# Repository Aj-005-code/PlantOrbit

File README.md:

# PlantOrbit-Sim — simulation of a self-calibrating orbital plant-imaging robot

**Everything in this project is SIMULATED.** No number here was measured on hardware. Never describe
these results as experimental or measured results in a patent specification, pitch or paper.

## 1. What the simulation is meant to support

The narrowed invention (see the earlier discussion) has three linked parts:

1. **Self-calibration** — a wheeled robot measures the pot (ranging-sensor scan + robust circle fit) and
   computes its own orbit radius and station list. No hardcoded pot size.
2. **Repeatable station poses** — the robot returns to the same angular stations every session. Dead
   reckoning drifts, so a fiducial (printed-marker) pose fix on the mat bounds the error.
3. **Multi-view change detection** — images taken at the *same* stations on different days are compared;
   an alert needs agreement from at least *k* of the 12 stations.

The three experiments test one question each:

| Exp | Question | Script |
|---|---|---|
| 1 | Does the scan + fit recover the pot radius for different pot sizes, with noise and leaf outliers? | `experiments/exp1_calibration.py` |
| 2 | Does the fiducial correction keep station poses repeatable where dead reckoning drifts? | `experiments/exp2_repeatability.py` |
| 3 | Does that repeatability reduce false alarms in image-based change detection while keeping detection power? | `experiments/exp3_change_detection.py` |

## 2. Environment setup (step by step)

Requirements: Python 3.10 or newer (built and tested on 3.12), about 500 MB disk, any OS, no GPU.

```bash
# 1. unzip the project and enter it
cd plantorbit-sim

# 2. create an isolated environment
python -m venv .venv
#   Windows PowerShell:  .venv\Scripts\Activate.ps1
#   Windows cmd:         .venv\Scripts\activate.bat
#   macOS / Linux:       source .venv/bin/activate

# 3. install pinned-minimum dependencies
pip install -r requirements.txt

# 4. run the tests (should print: 6 passed)
python -m pytest -q tests

# 5. run everything (about 4 minutes on a laptop CPU)
python run_all.py
```

Outputs appear in `results/`:

- `SUMMARY.md` — readable tables; `summary.json` — all numbers
- `exp*.csv` — raw and aggregated data (every table in your documents should trace to one of these)
- `figures/fig0..fig4*.png` — layout, calibration, repeatability, alert rates, station montage
- `environment.json` — library versions, full config, timestamp, SHA-256 hash of every result file

## 3. Code map

| File | Role |
|---|---|
| `orbitsim/config.py` | **Every assumption in one place** (sensor noise, slip, gyro drift, marker noise, thresholds) |
| `orbitsim/calibration.py` | Simulated ToF scan, least-squares and RANSAC circle fit, imaging radius, station generation |
| `orbitsim/robot.py` | Differential-drive model with separate TRUE and ESTIMATED pose; fiducial correction; session runner |
| `orbitsim/plant.py` | Procedural 3-D plant, five change scenarios, pinhole camera renderer, camera framing |
| `orbitsim/detect.py` | Pot-rim alignment, plant segmentation, per-station metrics, alert rules |
| `orbitsim/stats.py` | Wilson confidence interval, summary statistics |
| `experiments/` | The three experiments plus the layout figure |
| `tests/test_core.py` | Sanity tests (exact circle fit, zero-noise robot hits every station, markers help, determinism) |
| `run_all.py` | Runs everything and records a reproducibility manifest |

To change an assumption, edit `config.py` (for example `gyro_bias_sigma_dps`) and re-run. Every random
draw is seeded from `Config.seed`, so identical code and config give identical results.

## 4. Results from the final run (seed 20261011)

### Experiment 1 — calibration (500 random pots, radius 30–120 mm, offset up to 15 mm; 3 mm noise, 5 % dropout, 8 % leaf outliers)

- Robust (RANSAC) fit: radius error median 0.27 mm, 95th percentile 0.82 mm, max 1.27 mm; 100 % within 3 mm.
- Plain least squares on the same scans: only 69 % within 3 mm, because leaf outliers bias it.
- **Honest finding:** with *no* outliers and high sensor noise (6–10 mm), plain least squares is slightly
  *better* than RANSAC (for example 10 mm noise, no outliers: median 1.0 mm vs 1.95 mm), because the 6 mm
  inlier tolerance throws away good points. The robust fit pays off only when outliers exist. Tune
  `ransac_tol_mm` to your real sensor once measured.

### Experiment 2 — repeatability (200 sessions per mode, 12 stations, assumed hobby-grade robot)

| Mode | Mean position error | 95th pct | Same-station offset between two sessions, 95th pct |
|---|---|---|---|
| Dead reckoning (gyro + encoders, dock-homed) | 7.6 mm | 17.5 mm | 26.4 mm |
| Fiducial-corrected | 1.7 mm | 3.3 mm | 4.7 mm |

- Dead-reckoning error grows along the orbit (Fig. 2); the fiducial-corrected error stays flat.
- Sensitivity: with a 10× worse gyro bias (0.1 °/s), dead-reckoning mean error rises to 15.5 mm (95th pct 46 mm)
  while the corrected mode is unchanged (1.6 mm). The corrected mode scales with marker measurement noise
  instead (1 mm noise → 1.1 mm error; 5 mm → 5.5 mm).
- **Assumption warning:** these numbers depend entirely on the noise model in `config.py`. A better gyro,
  a stepper-based drive or a mechanical guide ring would shrink the dead-reckoning baseline. The
  comparison is "naive dead reckoning vs fiducial correction", not "every possible alternative".

### Experiment 3 — change detection (40 random plants, 5 scenarios, 12 stations, alert needs ≥ 3 stations)

| Scenario | Ideal poses | Dead reckoning | Fiducial-corrected |
|---|---|---|---|
| none (must NOT alert) | 0 % | **45 %** | 0 % |
| growth (must NOT alert) | 0 % | 5 % | 0 % |
| leaf drop (should alert) | 85 % | 90 % | 93 % |
| yellowing (should alert) | 100 % | 100 % | 100 % |
| wilting (should alert) | 100 % | 100 % | 100 % |

- The key result is the **false-alarm rate on an unchanged plant**: 45 % with dead reckoning versus 0/40
  (95 % interval 0–9 %) with fiducial correction.
- Read the dead-reckoning detection rates with care: they are inflated, because that mode raises alerts
  even when nothing changed. Detection power only means something together with the false-alarm rate.
- Threshold sweep (`exp3_threshold_sweep.csv`, area threshold 0.06): requiring more stations to agree cuts
  dead-reckoning false alarms (44 % at k=1, 25 % at k=3, 9 % at k=5) but never reaches the corrected mode's 0 %.
  Corrected-mode detection stays at 92–98 % across k=1–5.
- Leaf-drop detection (about 93 %) is the weakest case, since removing 3 of 22 leaves changes few pixels
  from some angles. Treat 40 trials as a small sample; the intervals in `exp3_alert_rates.csv` are wide.

## 5. Development log (keep this kind of record — it is good practice and honest)

1. **First full run:** the corrected mode and even the *ideal* mode showed 12–17 % false alarms on
   unchanged plants.
2. **Diagnosis** (inspecting `exp3_raw_metrics.csv` and a rendered frame): the camera framing left only a
   thin sliver of the pot in view, so the pot-rim alignment anchor was unstable and sometimes misaligned
   the image pair. This was a flaw in my set-up, not in the idea.
3. **Fixes:** (a) camera height and tilt are now chosen once per plant so canopy and pot rim both fit
   (`plant.framing`); (b) alignment is skipped when fewer than 300 pot pixels are visible or the proposed
   shift exceeds 25 px; (c) focal length changed 250 → 220 px for a wider field of view.
4. **Re-validation:** the fix was checked on a separate development seed (`seed+33`), then the final
   experiment was run on a **fresh test seed (`seed+4`)** so results were not tuned on the data reported.
5. Thresholds (6 % area, 8 % yellow, 8 % canopy-top, k=3) were set a priori, not fitted to results; the
   sweep CSV shows sensitivity to them.

## 6. What this simulation does and does NOT show

**It supports:** the algorithms are logically consistent and workable; fiducial correction should bound
pose error under the assumed noise; bounded pose error should reduce false alarms in multi-view
comparison; calibration adapts to pot size without manual coordinates.

**It does not show:** real sensor behaviour (ToF returns off glossy pots, fiducial detection under glare,
shadows, wind or watering changes); real plant appearance (the plant is a simple procedural model, not a
photograph of a living plant); non-circular pots (square or tapered pots break the circle assumption);
marker visibility from all 12 stations (assumed: at least two fiducials are always visible to a pose
camera, which is a hardware design detail to settle); real drift (measure your own robot).

## 7. Patent-readiness checklist

Not legal advice — confirm every step with a registered patent agent.

1. **Do not disclose before filing.** No GitHub push, video, post or paper until the provisional is filed.
2. **Version control privately:** `git init`, commit this project, `git tag sim-v1-final-run`. Commit
   timestamps give a dated record of what you had and when. Keep the repo private.
3. **Inventor's notebook:** one dated entry per work session (what you tried, what failed, what changed).
   Section 5 above is the model. Record who contributed which idea — inventorship matters.
4. **Check your institution's IP policy** (VIT) before using lab space, funds or staff time.
5. **Archive the run:** keep `results/environment.json` (library versions, config, file hashes) and the
   exact zip you worked from.
6. **Map results to the provisional specification:**

| Specification section | Source in this project |
|---|---|
| Background / problem | Fixed-coordinate systems fail across pot sizes; dead reckoning drifts; single-image checks miss trends |
| Summary of the invention | Sections 1 and 3 of this README |
| Brief description of drawings | `fig0_layout`, flowcharts you draw from `calibration.py` and `robot.py`, block diagram, pin diagram |
| Detailed description / enablement | The algorithms, parameters and assumptions in `config.py`, written out in words and pseudocode |
| Examples | Experiments 1–3, **explicitly labelled as simulation**, with the noise model stated |
| Claims | Method claims: scan → fit → derive orbit; fiducial-corrected station revisit; same-station multi-view comparison with k-of-n agreement. Draft with your agent. |

7. **Plot figures properly:** the PNGs here are evidence figures, not formal patent drawings. Formal drawings
   are black-and-white line drawings; your agent will advise.
8. **Prior art:** the earlier search was informal. A professional IPC-coded search is still needed before
   finalising claims, and linear-rail repeatable-pose systems (found earlier) are the closest art to
   distinguish against.
9. **File order:** DPIIT startup registration → provisional application at ipindiaonline.gov.in →
   12 months to replace simulated evidence with measured data and file the complete specification.

## 8. Replacing each assumption with a measurement (the next 12 months)

| Simulated assumption (`config.py`) | How to measure it on hardware |
|---|---|
| `tof_noise_mm`, dropout, outliers | Scan 5 real pots (matte, glossy, different heights) 50 times each; log error vs a ruler |
| `slip_*`, `lateral_sigma_frac` | Command 1 m straight and a full circle 30 times on your desk; measure the final position |
| `gyro_bias_sigma_dps`, `gyro_arw` | Log the stationary MPU6050 gyro for 10 minutes after calibration; fit drift |
| `dock_pos_sigma` | Dock 30 times; measure offset |
| `marker_pos_sigma`, visibility | Photograph the mat from each station; compare marker-derived pose to a ruler/protractor |
| Plant appearance | Image a real plant over weeks; rerun `detect.py` on real photos |
| Thresholds | Choose from real null (unchanged-plant) image pairs, then test on separate days |

When these are measured, update `config.py`, re-run, and report the measured values alongside the simulated ones.

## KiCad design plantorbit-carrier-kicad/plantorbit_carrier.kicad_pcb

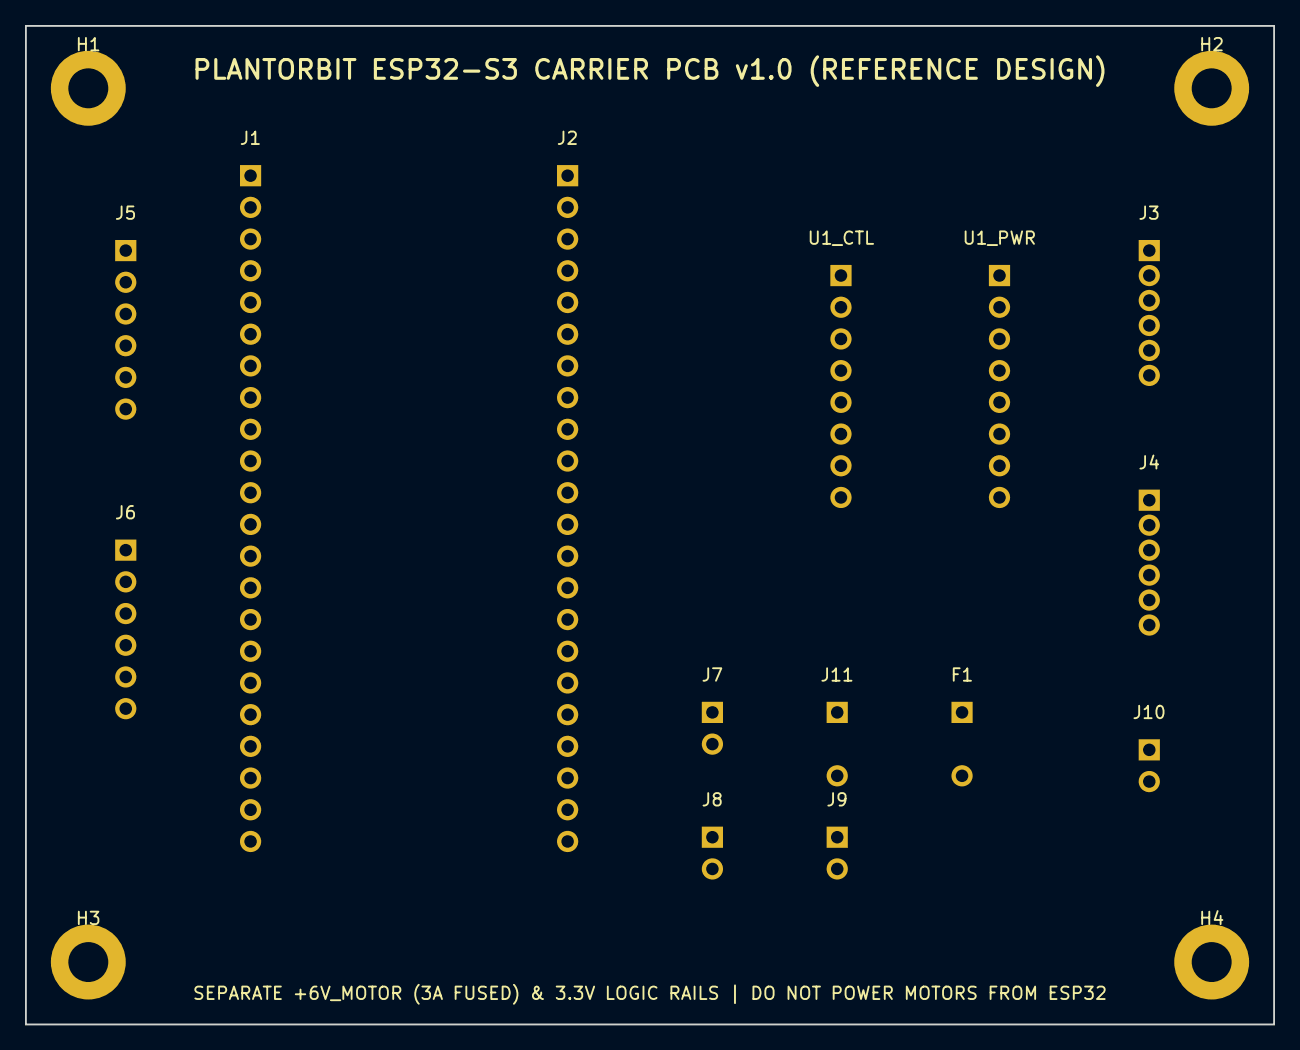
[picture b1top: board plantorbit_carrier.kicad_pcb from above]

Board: 2 copper layers, 100.0 x 80.0 mm, 18 parts (0 on the bottom side), 26 nets, no tracks yet.

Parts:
F1: FUSE_3A_MOTOR; PinHeader_1x02_P5.08mm_Vertical
H1, H2, H3, H4: M3_Mount; MountingHole_3.2mm_M3_Pad
J1: ESP32S3_LEFT_22P; PinHeader_1x22_P2.54mm_Vertical
J2: ESP32S3_RIGHT_22P; PinHeader_1x22_P2.54mm_Vertical
J3: POLOLU_5141_LEFT; PinHeader_1x06_P2.00mm_Vertical
J4: POLOLU_5141_RIGHT; PinHeader_1x06_P2.00mm_Vertical
J5: VL53L1X_I2C_0x29; PinHeader_1x06_P2.54mm_Vertical
J6: MPU6050_I2C_0x68; PinHeader_1x06_P2.54mm_Vertical
J7: ESTOP_STATUS; PinHeader_1x02_P2.54mm_Vertical
J8: BUMPER_LEFT; PinHeader_1x02_P2.54mm_Vertical
J9: BUMPER_RIGHT; PinHeader_1x02_P2.54mm_Vertical
J10: HIGH_CRI_LED; PinHeader_1x02_P2.54mm_Vertical
J11: +6V_MOTOR_IN_3A; PinHeader_1x02_P5.08mm_Vertical
U1_CTL: TB6612FNG_CTL; PinHeader_1x08_P2.54mm_Vertical
U1_PWR: TB6612FNG_OUT; PinHeader_1x08_P2.54mm_Vertical

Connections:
+3V3: J1.1, J1.2, J3.4, J4.4, J5.1, J6.1, U1_PWR.2
+6V_MOTOR: F1.2, J10.1, U1_PWR.1
+6V_MOTOR_RAW: F1.1, J11.1
BUMPER_LEFT_N: J2.5, J8.1
BUMPER_RIGHT_N: J2.9, J9.1
ENC_LEFT_A: J1.16, J3.3
ENC_LEFT_B: J1.17, J3.2
ENC_RIGHT_A: J1.18, J4.3
ENC_RIGHT_B: J1.19, J4.2
ESTOP_SENSE: J2.4, J7.1
GND: H1.1, H2.1, H3.1, H4.1, J1.22, J2.1, J2.21, J2.22, J3.1, J4.1, J5.2, J6.2, J6.5, J7.2, J8.2, J9.2, J11.2, U1_CTL.8, U1_PWR.3, U1_PWR.8
I2C_SCL: J1.15, J5.3, J6.3
I2C_SDA: J1.12, J5.4, J6.4
MOT_LEFT_M1: J3.6, U1_PWR.4
MOT_LEFT_M2: J3.5, U1_PWR.5
MOT_RIGHT_M1: J4.6, U1_PWR.7
MOT_RIGHT_M2: J4.5, U1_PWR.6
TB6612_AIN1: J1.5, U1_CTL.3
TB6612_AIN2: J1.6, U1_CTL.2
TB6612_BIN1: J1.8, U1_CTL.5
TB6612_BIN2: J1.9, U1_CTL.6
TB6612_PWMA: J1.4, U1_CTL.1
TB6612_PWMB: J1.7, U1_CTL.7
TB6612_STBY: J1.10, U1_CTL.4
TOF_INT: J1.11, J5.5
TOF_XSHUT: J2.18, J5.6

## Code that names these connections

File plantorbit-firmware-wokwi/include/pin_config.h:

#ifndef PLANTORBIT_PIN_CONFIG_H
#define PLANTORBIT_PIN_CONFIG_H

// =============================================================================
// PLANTORBIT PIN MAPPING CONFIGURATION (ESP32-S3-DevKitC-1, 44-pin)
// Matches Section 4 of Locked Architecture Plan (Plan.pdf)
// Select backend via build flag: -DHAL_BACKEND_WOKWI=1 or -DHAL_BACKEND_TARGET=1
// Default in Wokwi browser simulator: HAL_BACKEND_WOKWI
// =============================================================================

#if !defined(HAL_BACKEND_WOKWI) && !defined(HAL_BACKEND_TARGET)
#define HAL_BACKEND_WOKWI 1
#endif

// ---- Shared Pins Across Both Backends ----
#define PIN_I2C_SDA          8   // GPIO8:  I2C SDA (MPU6050 0x68 + Target VL53L1X 0x29)
#define PIN_I2C_SCL          9   // GPIO9:  I2C SCL (MPU6050 0x68 + Target VL53L1X 0x29)
#define PIN_ILLUM_LED_EN    14   // GPIO14: White LED-ring MOSFET gate (Target) / Sim LED (Wokwi)
#define PIN_ESTOP_STATUS     1   // GPIO1:  E-Stop auxiliary sense contact (Active LOW w/ pullup)
#define PIN_BUMPER_LEFT      2   // GPIO2:  Left collision bumper microswitch (Active LOW)
#define PIN_BUMPER_RIGHT    39   // GPIO39: Right collision bumper microswitch (Active LOW)

// ---- Backend-Specific Pin Assignments ----
#if defined(HAL_BACKEND_TARGET) && (HAL_BACKEND_TARGET == 1)
  // === ACTUAL TARGET HARDWARE BACKEND (KiCad Carrier PCB) ===
  // Motor Driver: Toshiba/SparkFun TB6612FNG Dual H-Bridge
  #define PIN_TB6612_PWMA    4   // GPIO4:  Left motor PWM
  #define PIN_TB6612_AIN1    5   // GPIO5:  Left motor direction input 1
  #define PIN_TB6612_AIN2    6   // GPIO6:  Left motor direction input 2
  #define PIN_TB6612_PWMB    7   // GPIO7:  Right motor PWM
  #define PIN_TB6612_BIN1   15   // GPIO15: Right motor direction input 1
  #define PIN_TB6612_BIN2   16   // GPIO16: Right motor direction input 2
  #define PIN_TB6612_STBY   17   // GPIO17: TB6612FNG standby/enable (Active HIGH)

  // Quadrature Encoders: Pololu #5141 (150.58:1 MP 6V with 12 CPR encoder, 3.3V Vcc)
  #define PIN_ENC_LEFT_A    10   // GPIO10: Left encoder channel A
  #define PIN_ENC_LEFT_B    11   // GPIO11: Left encoder channel B
  #define PIN_ENC_RIGHT_A   12   // GPIO12: Right encoder channel A
  #define PIN_ENC_RIGHT_B   13   // GPIO13: Right encoder channel B

  // Range Sensor: ST/Adafruit VL53L1X ToF (I2C 0x29)
  #define PIN_TOF_INT       18   // GPIO18: Optional VL53L1X GPIO1 interrupt (Active LOW)
  #define PIN_TOF_XSHUT     21   // GPIO21: Optional VL53L1X XSHUT shutdown control
#else
  // === WOKWI SIMULATION SUBSTITUTE BACKEND ===
  // Drive Proxy: Two A4988 Stepper Drivers + Two Bipolar Stepper Motors
  #define PIN_WOKWI_L_STEP   4   // GPIO4:  Left A4988 STEP
  #define PIN_WOKWI_L_DIR    5   // GPIO5:  Left A4988 DIR
  #define PIN_WOKWI_R_STEP   6   // GPIO6:  Right A4988 STEP
  #define PIN_WOKWI_R_DIR    7   // GPIO7:  Right A4988 DIR

  // Range Proxy: HC-SR04 Ultrasonic Sensor (exercises calibration state machine)
  // NOTE: On physical hardware HC-SR04 ECHO is 5V and requires a level shifter;
  // in Wokwi it is a simulation-only substitute for the 3.3V I2C VL53L1X.
  #define PIN_WOKWI_SR04_ECHO 18 // GPIO18: HC-SR04 ECHO input
  #define PIN_WOKWI_SR04_TRIG 21 // GPIO21: HC-SR04 TRIG output
#endif

// ---- Robot Geometric & Kinematic Constants (Reference Design) ----
#define WHEEL_DIAMETER_MM       45.0f   // 40-50 mm rubber wheel nominal diameter
#define WHEEL_TRACK_MM         190.0f   // Differential-drive wheel track width
#define POLOLU_5141_CPR         12.0f   // Motor shaft counts per revolution
#define POLOLU_5141_GEAR_RATIO 150.58f  // Exact gear ratio: (25*32*34*35*38)/(12*11*14*13*10)
#define COUNTS_PER_WHEEL_REV   (POLOLU_5141_CPR * POLOLU_5141_GEAR_RATIO) // ~1806.96 counts/rev

#define DEFAULT_SCAN_RADIUS_MM 250.0f
#define DEFAULT_STANDOFF_MM    180.0f
#define DEFAULT_N_STATIONS      12
#define CAM_OFFSET_FORWARD_MM   35.0f   // Rigid inward-facing camera optical center offset

#endif // PLANTORBIT_PIN_CONFIG_H
